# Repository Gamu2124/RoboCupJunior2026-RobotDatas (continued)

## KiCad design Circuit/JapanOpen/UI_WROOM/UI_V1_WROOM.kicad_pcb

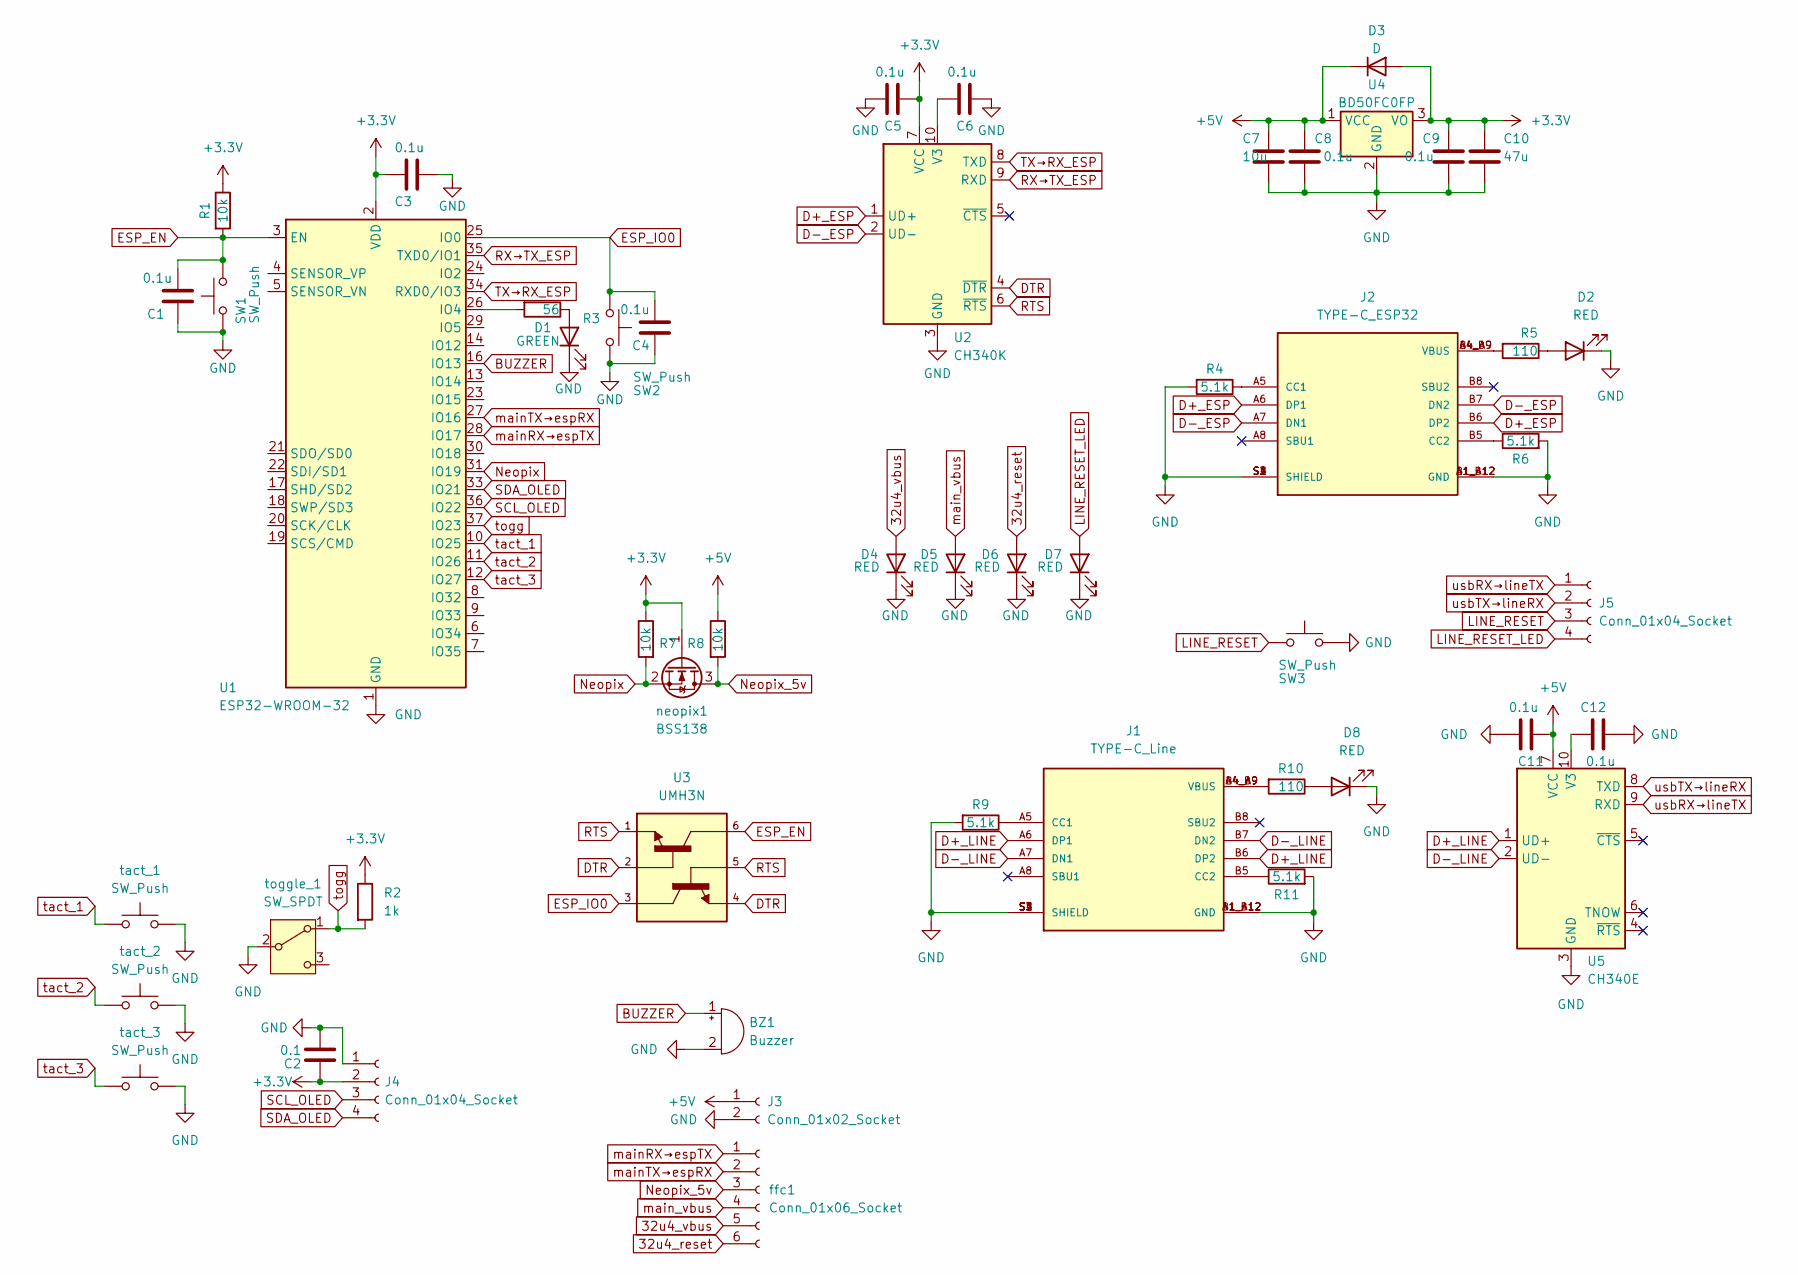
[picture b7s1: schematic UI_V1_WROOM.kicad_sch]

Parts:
BZ1: Buzzer; XDCR_KXG0909P
C1, C3, C4, C5, C6, C8, C9, C11, C12: 0.1u; C_0603_1608Metric_Pad1.08x0.95mm_HandSolder; LCSC C1581
C2: 0.1; C_0603_1608Metric_Pad1.08x0.95mm_HandSolder; LCSC C1581
C7: 10u; C_Disc_D5.1mm_W3.2mm_P5.00mm; LCSC C1713
C10: 47u; CP_Radial_D5.0mm_P2.00mm; LCSC C3337
D1: GREEN; LED_0603_1608Metric_Pad1.05x0.95mm_HandSolder
D2, D4, D5, D6, D7, D8: RED; LED_0603_1608Metric_Pad1.05x0.95mm_HandSolder
D3: D; D_SOD-123F
J1: TYPE-C_Line; NELTRON_5077CR-16SMC2-BK-TR; PARTREV B
J2: TYPE-C_ESP32; NELTRON_5077CR-16SMC2-BK-TR; PARTREV B
J3: Conn_01x02_Socket; JST_XH_B2B-XH-A_1x02_P2.50mm_Vertical
J4: Conn_01x04_Socket; PinSocket_1x04_P2.54mm_Vertical
J5: Conn_01x04_Socket; JST_XH_S4B-XH-A_1x04_P2.50mm_Horizontal
R1: 10k; R_1206_3216Metric; LCSC C26033
R2: 1k; R_Axial_DIN0207_L6.3mm_D2.5mm_P10.16mm_Horizontal
R3: 56; R_1206_3216Metric; LCSC C17909
R4, R6, R9, R11: 5.1k; R_0603_1608Metric_Pad0.98x0.95mm_HandSolder; LCSC C26033
R5, R10: 110; R_1206_3216Metric; LCSC C17909
R7, R8: 10k; R_1206_3216Metric; LCSC C1489
SW1, SW2, SW3: SW_Push; Switch_SKRPABE010
U1: ESP32-WROOM-32
U2: CH340K; SSOP-10-1EP_3.9x4.9mm_P1mm_EP2.1x3.3mm
U3: UMH3N; UMT6
U4: BD50FC0FP; TO-252-2
U5: CH340E; MSOP-10_3x3mm_P0.5mm
ffc1: Conn_01x06_Socket; TE_84952-6_1x06-1MP_P1.0mm_Horizontal
neopix1: BSS138; SOT-23; LCSC C192057
tact_1, tact_2, tact_3: SW_Push; SW_PUSH-12mm
toggle_1: SW_SPDT; PinSocket_1x03_P2.54mm_Vertical

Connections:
32u4_reset: D6.2 (A), ffc1.6
32u4_vbus: D4.2 (A), ffc1.5
+3.3V: C2.1, C3.2, C5.1, C9.1, C10.1, D3.2 (A), J4.2, R1.1, R2.1, R7.1, U1.2 (VDD), U2.7 (VCC), U4.3 (VO), neopix1.1 (G)
+5V: C7.1, C8.1, C11.1, D3.1 (K), J3.1, R8.1, U4.1 (VCC), U5.7 (VCC)
BUZZER: BZ1.1 (+), BZ1.P, U1.16 (IO13)
D+_ESP: J2.A6 (DP1), J2.B6 (DP2), U2.1 (UD+)
D+_LINE: J1.A6 (DP1), J1.B6 (DP2), U5.1 (UD+)
D-_ESP: J2.A7 (DN1), J2.B7 (DN2), U2.2 (UD-)
D-_LINE: J1.A7 (DN1), J1.B7 (DN2), U5.2 (UD-)
DTR: U2.4 (~DTR), U3.2, U3.4
ESP_EN: C1.1, R1.2, SW1.1, U1.3 (EN), U3.6
ESP_IO0: C4.1, SW2.1, U1.25 (IO0), U3.3
GND: BZ1.2 (-), BZ1.N, C1.2, C2.2, C3.1, C4.2, C5.2, C6.1, C7.2, C8.2, C9.2, C10.2, C11.2, C12.2, D1.1 (K), D2.1 (K), D4.1 (K), D5.1 (K), D6.1 (K), D7.1 (K), D8.1 (K), J1.A1_B12 (GND), J1.B1_A12 (GND), J1.S1 (SHIELD), J1.S2 (SHIELD), J1.S3 (SHIELD), J1.S4 (SHIELD), J2.A1_B12 (GND), J2.B1_A12 (GND), J2.S1 (SHIELD), J2.S2 (SHIELD), J2.S3 (SHIELD), J2.S4 (SHIELD), J3.2, J4.1, R4.2, R6.2, R9.2, R11.2, SW1.2, SW2.2, SW3.2, U1.1 (GND), U1.15 (GND), U1.38 (GND), U1.39 (GND), U2.3 (GND), U2.11 (GND), U4.2 (GND), U5.3 (GND), tact_1.2, tact_2.2, tact_3.2, toggle_1.2 (B)
LINE_RESET: J5.3, SW3.1
LINE_RESET_LED: D7.2 (A), J5.4
Neopix: R7.2, U1.31 (IO19), neopix1.2 (S)
Neopix_5v: R8.2, ffc1.3, neopix1.3 (D)
unnamed: D1.2 (A), R3.1
unnamed: D2.2 (A), R5.1
unnamed: D8.2 (A), R10.1
unnamed: J1.A5 (CC1), R9.1
unnamed: J1.B5 (CC2), R11.1
unnamed: J1.A4_B9 (VBUS), J1.B4_A9 (VBUS), R10.2
unnamed: J2.A5 (CC1), R4.1
unnamed: J2.B5 (CC2), R6.1
unnamed: J2.A4_B9 (VBUS), J2.B4_A9 (VBUS), R5.2
unnamed: R3.2, U1.26 (IO4)
unnamed: C6.2, U2.10 (V3)
unnamed: C12.1, U5.10 (V3)
RTS: U2.6 (~RTS), U3.1, U3.5
RX→TX_ESP: U1.35 (TXD0/IO1), U2.9 (RXD)
SCL_OLED: J4.3, U1.36 (IO22)
SDA_OLED: J4.4, U1.33 (IO21)
TX→RX_ESP: U1.34 (RXD0/IO3), U2.8 (TXD)
mainRX→espTX: U1.28 (IO17), ffc1.1
mainTX→espRX: U1.27 (IO16), ffc1.2
main_vbus: D5.2 (A), ffc1.4
tact_1: U1.10 (IO25), tact_1.1
tact_2: U1.11 (IO26), tact_2.1
tact_3: U1.12 (IO27), tact_3.1
togg: R2.2, U1.37 (IO23), toggle_1.1 (A)
usbRX→lineTX: J5.1, U5.9 (RXD)
usbTX→lineRX: J5.2, U5.8 (TXD)

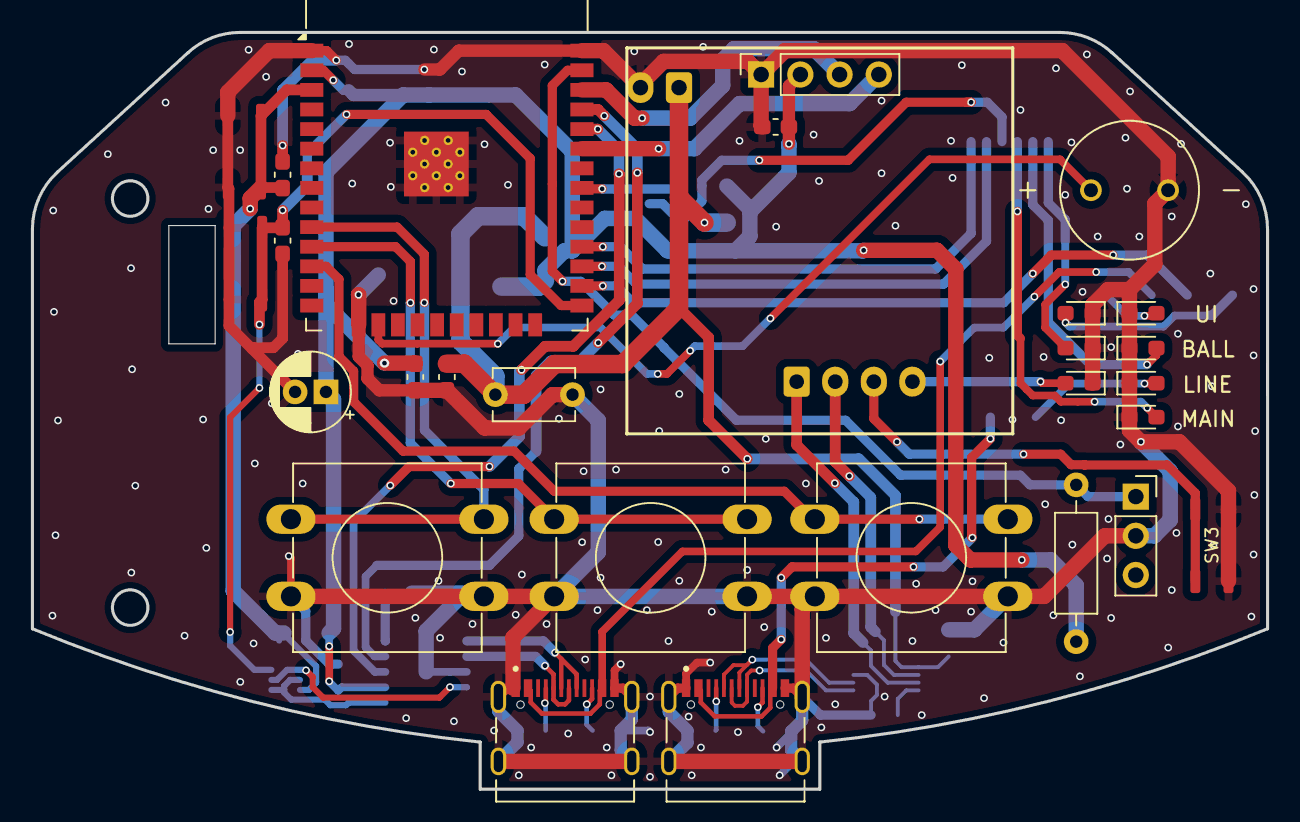
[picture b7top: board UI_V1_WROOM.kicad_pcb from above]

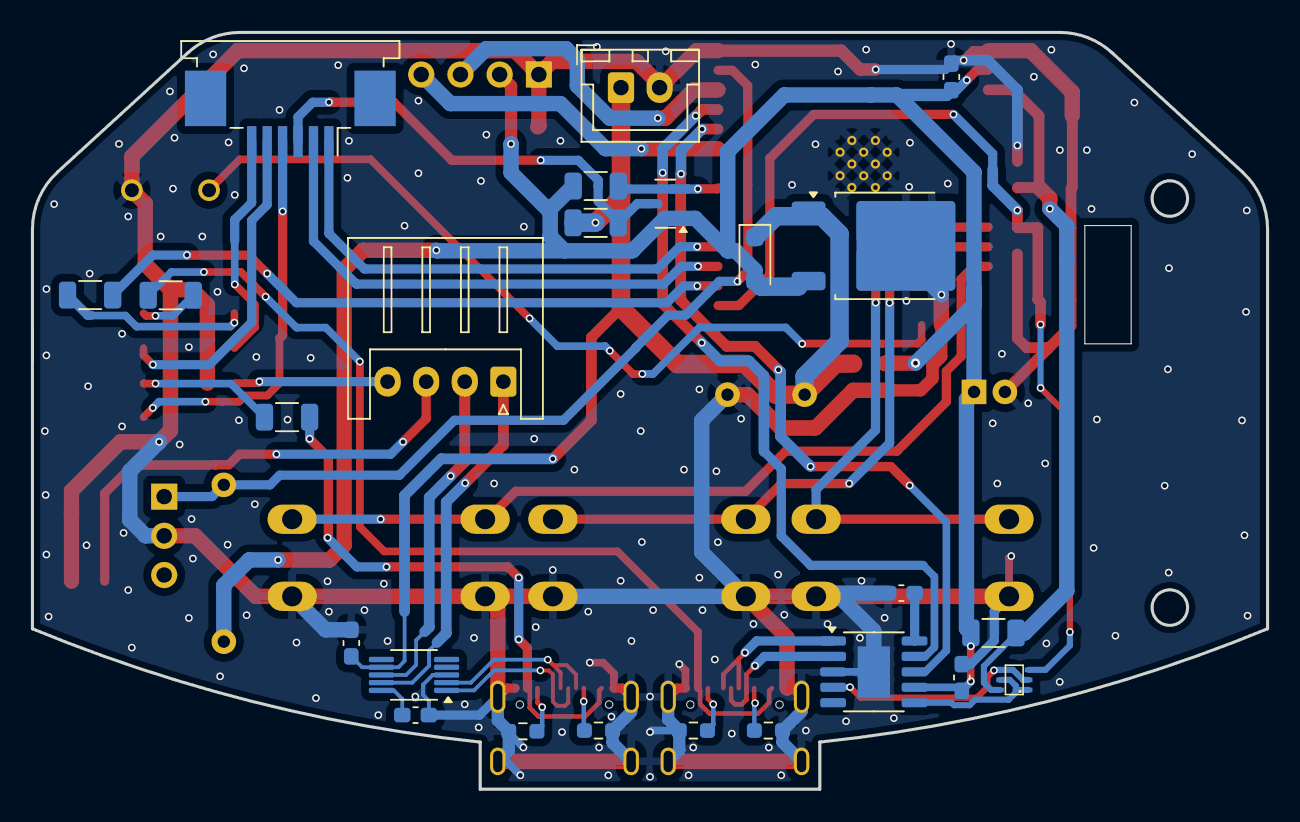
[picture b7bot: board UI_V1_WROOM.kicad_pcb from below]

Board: 2 copper layers, 80.0 x 49.0 mm, 51 parts (24 on the bottom side), 43 nets.

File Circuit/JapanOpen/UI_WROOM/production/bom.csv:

Designator,Footprint,Quantity,Value,LCSC Part #
BZ1,XDCR_KXG0909P,1,Buzzer,
"C1, C11, C12, C3, C4, C5, C6, C8, C9",0603,9,0.1u,C1581
C10,CP_Radial_D5.0mm_P2.00mm,1,47u,C3337
C2,0603,1,0.1,C1581
C7,C_Disc_D5.1mm_W3.2mm_P5.00mm,1,10u, C1713
D1,0603,1,GREEN,
"D2, D4, D5, D6, D7, D8",0603,6,RED,
D3,D_SOD-123F,1,D,
FFC1,TE_84952-6_1x06-1MP_P1.0mm_Horizontal,1,Conn_01x06_Socket,
J1,NELTRON_5077CR-16SMC2-BK-TR,1,TYPE-C_Line,
J2,NELTRON_5077CR-16SMC2-BK-TR,1,TYPE-C_ESP32,
J3,JST_XH_B2B-XH-A_1x02_P2.50mm_Vertical,1,Conn_01x02_Socket,
J4,PinSocket_1x04_P2.54mm_Vertical,1,Conn_01x04_Socket,
J5,JST_XH_S4B-XH-A_1x04_P2.50mm_Horizontal,1,Conn_01x04_Socket,
NEOPIX1,SOT-23,1,BSS138, C192057
R1,1206,1,10k,C26033
"R10, R5",1206,2,110,C17909
"R11, R4, R6, R9",0603,4,5.1k,C26033
R2,R_Axial_DIN0207_L6.3mm_D2.5mm_P10.16mm_Horizontal,1,1k,
R3,1206,1,56,C17909
"R7, R8",1206,2,10k, C1489
"SW1, SW2, SW3",Switch_SKRPABE010,3,SW_Push,
"TACT_1, TACT_2, TACT_3",SW_PUSH-12mm,3,SW_Push,
TOGGLE_1,PinSocket_1x03_P2.54mm_Vertical,1,SW_SPDT,
U1,ESP32-WROOM-32,1,ESP32-WROOM-32,
U2,SSOP-10-1EP_3.9x4.9mm_P1mm_EP2.1x3.3mm,1,CH340K,
U3,UMT6,1,UMH3N,
U4,TO-252-2,1,BD50FC0FP,
U5,MSOP-10_3x3mm_P0.5mm,1,CH340E,

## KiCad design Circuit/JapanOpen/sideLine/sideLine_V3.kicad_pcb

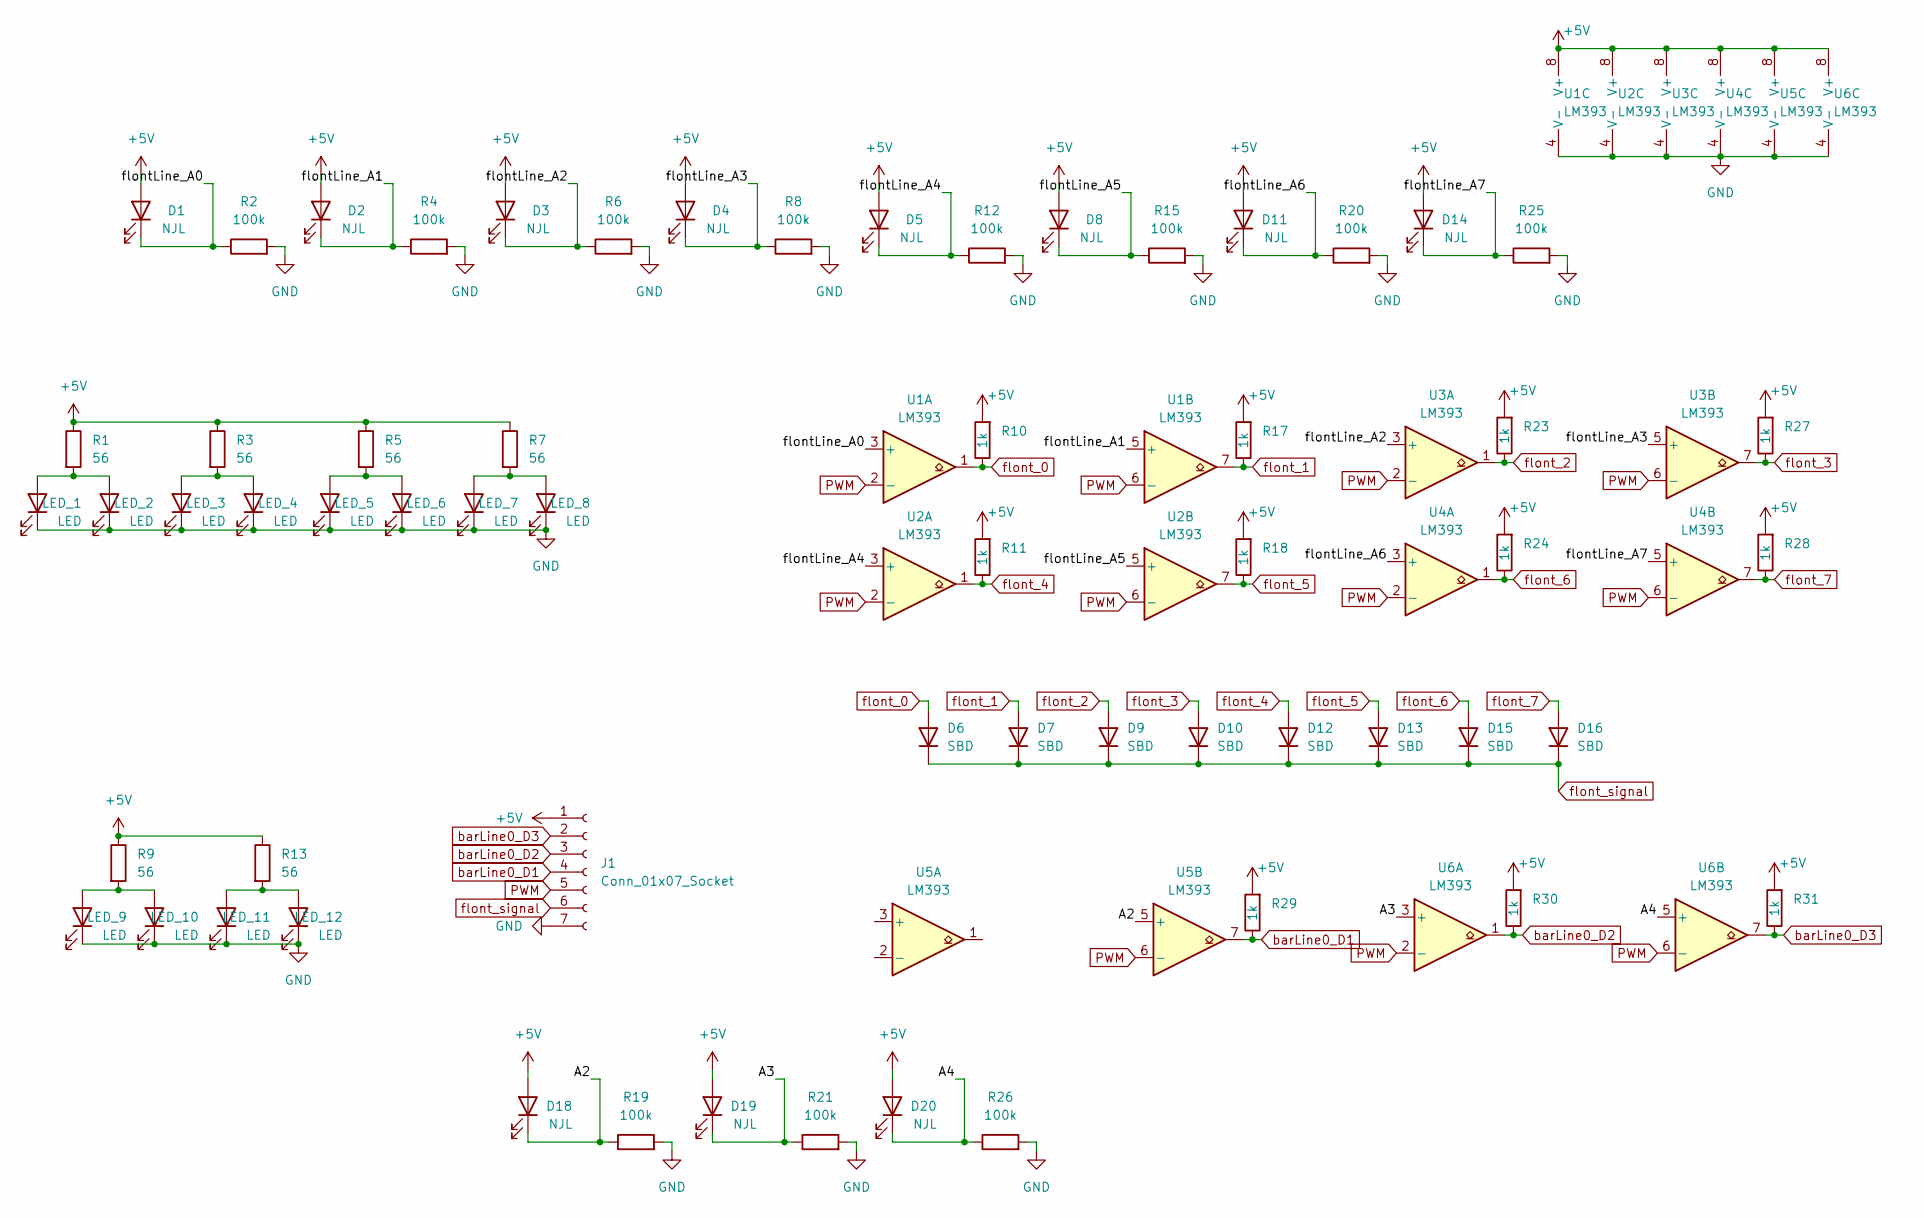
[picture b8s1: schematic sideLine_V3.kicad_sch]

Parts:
D1, D2, D3, D4, D5, D8, D11, D14, D18, D19, D20: NJL; LED_0603_1608Metric
D6, D7, D9, D10, D12, D13, D15, D16: SBD; D_SOD-323
J1: Conn_01x07_Socket; PinSocket_1x07_P2.54mm_Vertical
LED_1, LED_2, LED_3, LED_4, LED_5, LED_6, LED_7, LED_8, LED_9, LED_10, LED_11, LED_12: LED; LED_0603_1608Metric_Pad1.05x0.95mm_HandSolder
R1, R3, R5, R7, R9, R13: 56; R_1206_3216Metric; LCSC C17995
R2, R4, R6, R8, R12, R15, R19, R20, R21, R25, R26: 100k; R_0603_1608Metric; LCSC C23098
R10, R11, R17, R18, R23, R24, R27, R28, R29, R30, R31: 1k; R_0603_1608Metric; LCSC C23098
U1, U2, U3, U4, U5, U6: LM393; SOIC-8_3.9x4.9mm_P1.27mm

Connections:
+5V: D1.2 (A), D2.2 (A), D3.2 (A), D4.2 (A), D5.2 (A), D8.2 (A), D11.2 (A), D14.2 (A), D18.2 (A), D19.2 (A), D20.2 (A), J1.1, R1.1, R3.1, R5.1, R7.1, R9.1, R10.2, R11.2, R13.1, R17.2, R18.2, R23.2, R24.2, R27.2, R28.2, R29.2, R30.2, R31.2, U1.8 (V+), U2.8 (V+), U3.8 (V+), U4.8 (V+), U5.8 (V+), U6.8 (V+)
/A2: D18.1 (K), R19.1, U5.5 (+)
/A3: D19.1 (K), R21.1, U6.3 (+)
/A4: D20.1 (K), R26.1, U6.5 (+)
/flontLine_A0: D1.1 (K), R2.1, U1.3 (+)
/flontLine_A1: D2.1 (K), R4.1, U1.5 (+)
/flontLine_A2: D3.1 (K), R6.1, U3.3 (+)
/flontLine_A3: D4.1 (K), R8.1, U3.5 (+)
/flontLine_A4: D5.1 (K), R12.1, U2.3 (+)
/flontLine_A5: D8.1 (K), R15.1, U2.5 (+)
/flontLine_A6: D11.1 (K), R20.1, U4.3 (+)
/flontLine_A7: D14.1 (K), R25.1, U4.5 (+)
GND: J1.7, LED_1.1 (K), LED_2.1 (K), LED_3.1 (K), LED_4.1 (K), LED_5.1 (K), LED_6.1 (K), LED_7.1 (K), LED_8.1 (K), LED_9.1 (K), LED_10.1 (K), LED_11.1 (K), LED_12.1 (K), R2.2, R4.2, R6.2, R8.2, R12.2, R15.2, R19.2, R20.2, R21.2, R25.2, R26.2, U1.4 (V-), U2.4 (V-), U3.4 (V-), U4.4 (V-), U5.4 (V-), U6.4 (V-)
unnamed: LED_1.2 (A), LED_2.2 (A), R1.2
unnamed: LED_3.2 (A), LED_4.2 (A), R3.2
unnamed: LED_5.2 (A), LED_6.2 (A), R5.2
unnamed: LED_7.2 (A), LED_8.2 (A), R7.2
unnamed: LED_9.2 (A), LED_10.2 (A), R9.2
unnamed: LED_11.2 (A), LED_12.2 (A), R13.2
PWM: J1.5, U1.2 (-), U1.6 (-), U2.2 (-), U2.6 (-), U3.2 (-), U3.6 (-), U4.2 (-), U4.6 (-), U5.6 (-), U6.2 (-), U6.6 (-)
barLine0_D1: J1.4, R29.1, U5.7
barLine0_D2: J1.3, R30.1, U6.1
barLine0_D3: J1.2, R31.1, U6.7
flont_0: D6.2 (A), R10.1, U1.1
flont_1: D7.2 (A), R17.1, U1.7
flont_2: D9.2 (A), R23.1, U3.1
flont_3: D10.2 (A), R27.1, U3.7
flont_4: D12.2 (A), R11.1, U2.1
flont_5: D13.2 (A), R18.1, U2.7
flont_6: D15.2 (A), R24.1, U4.1
flont_7: D16.2 (A), R28.1, U4.7
flont_signal: D6.1 (K), D7.1 (K), D9.1 (K), D10.1 (K), D12.1 (K), D13.1 (K), D15.1 (K), D16.1 (K), J1.6

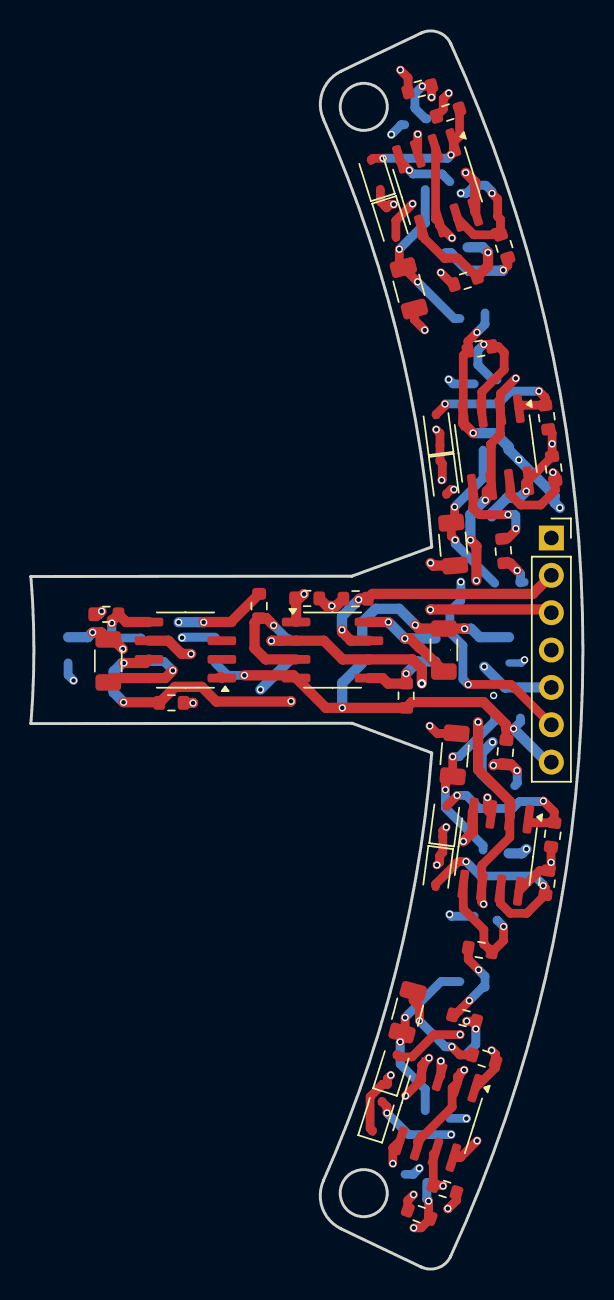
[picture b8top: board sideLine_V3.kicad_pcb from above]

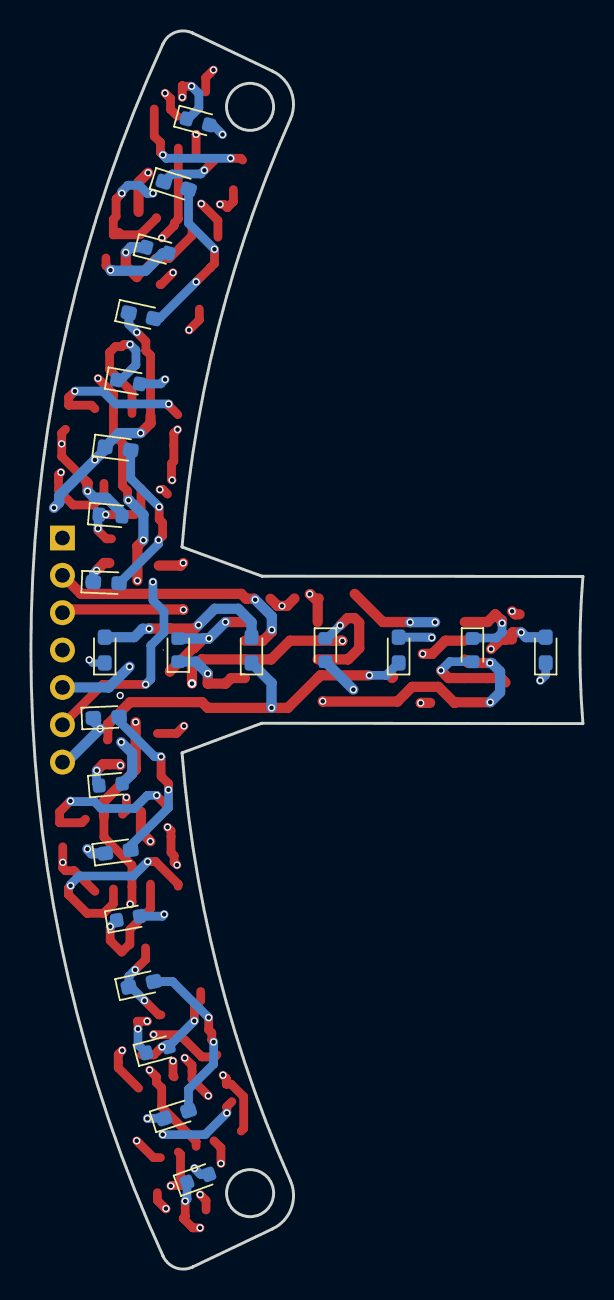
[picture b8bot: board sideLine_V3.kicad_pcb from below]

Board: 4 copper layers, 37.5 x 84.2 mm, 66 parts (23 on the bottom side), 32 nets.

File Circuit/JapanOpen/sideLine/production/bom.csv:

Designator,Footprint,Quantity,Value,LCSC Part #
"D1, D11, D14, D18, D19, D2, D20, D3, D4, D5, D8",0603,11,NJL,
"D10, D12, D13, D15, D16, D6, D7, D9",D_SOD-323,8,SBD,
J1,PinSocket_1x07_P2.54mm_Vertical,1,Conn_01x07_Socket,
"LED_1, LED_10, LED_11, LED_12, LED_2, LED_3, LED_4, LED_5, LED_6, LED_7, LED_8, LED_9",0603,12,LED,
"R1, R13, R3, R5, R7, R9",1206,6,56,C17995
"R10, R11, R17, R18, R23, R24, R27, R28, R29, R30, R31",0603,11,1k,C23098
"R12, R15, R19, R2, R20, R21, R25, R26, R4, R6, R8",0603,11,100k,C23098
"U1, U2, U3, U4, U5, U6",SOIC-8_3.9x4.9mm_P1.27mm,6,LM393,

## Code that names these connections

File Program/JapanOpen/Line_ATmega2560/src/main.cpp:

#include <Arduino.h>

// ピン情報の定義
volatile uint8_t* pins[] = {
  &PIND, &PIND, &PINL, &PINL, &PINL, &PINL, &PINH, &PINH,
  &PINH, &PINH, &PINH, &PINH, &PINJ, &PINJ, &PINJ, &PINJ,
  &PINJ, &PINC, &PINC, &PINC, &PINC, &PINC, &PINC, &PINC
};

uint8_t bits[] = {
  7, 6, 7, 6, 5, 4, 6, 5,
  4, 3, 2, 1, 7, 6, 5, 4,
  3, 7, 6, 5, 4, 3, 2, 1
};

// デバッグ表示用関数
void debugPrint(uint8_t b0, uint8_t b1, uint8_t b2, uint8_t side_grid);

void setup() {
  Serial.begin(9600);  // PCデバッグ用
  Serial1.begin(115200); // Teensy通信用
  // 入力ピン初期化
  DDRA &= ~(_BV(PA2) | _BV(PA6) | _BV(PA5));
  DDRD &= ~(_BV(PD7) | _BV(PD6));
  DDRL &= ~(_BV(PL7) | _BV(PL6) | _BV(PL5) | _BV(PL4));
  DDRH &= ~(_BV(PH6) | _BV(PH5) | _BV(PH4) | _BV(PH3) | _BV(PH2) | _BV(PH1));
  DDRJ &= ~(_BV(PJ7) | _BV(PJ6) | _BV(PJ5) | _BV(PJ4) | _BV(PJ3) | _BV(PJ0));
  DDRC &= ~(_BV(PC7) | _BV(PC6) | _BV(PC5) | _BV(PC4) | _BV(PC3) | _BV(PC2) | _BV(PC1));
  DDRF &= ~(_BV(PF0) | _BV(PF1) | _BV(PF3) | _BV(PF6));
  DDRK &= ~(_BV(PK0) | _BV(PK1) | _BV(PK4) | _BV(PK5) | _BV(PK6));
  pinMode(5, OUTPUT);
  TCCR3B = (TCCR3B & 0xF8) | 0x01; 
  analogWrite(5, 85); //26朝150 //80
}

void loop() {
  // unsigned long startTime = micros(); // 開始（マイクロ秒） 
  // 1. ラインセンサーパッキング
  uint8_t b0 = 0, b1 = 0, b2 = 0;
  for (int i = 0; i < 8; i++)  if ((*pins[i] >> bits[i]) & 0x01) b0 |= (1 << i);
  for (int i = 8; i < 16; i++) if ((*pins[i] >> bits[i]) & 0x01) b1 |= (1 << (i - 8));
  for (int i = 16; i < 24; i++)if ((*pins[i] >> bits[i]) & 0x01) b2 |= (1 << (i - 16));

  // 2. サイド & Gridパッキング
  uint8_t side_grid = 0;
  if ((PINA >> 2) & 0x01) side_grid |= (1 << 7); // F
  if ((PINF >> 6) & 0x01) side_grid |= (1 << 6); // L
  if ((PINA >> 6) & 0x01) side_grid |= (1 << 5); // R
  if ((PINA >> 5) & 0x01) side_grid |= (1 << 4); // B

  if (((PINF >> 0) | (PINF >> 1) | (PINF >> 3)) & 0x01) side_grid |= (1 << 3); // GL
  // if (((PINK >> 0) | (PINK >> 1) | (PINJ >> 0)) & 0x01) side_grid |= (1 << 2); // GR
  if (((PINK >> 4) | (PINK >> 5) | (PINK >> 6)) & 0x01) side_grid |= (1 << 1); // GB

  // 3. パケット送信 (6バイト)
  Serial1.write(255);       // Header
  Serial1.write(b0);
  Serial1.write(b1);
  Serial1.write(b2);
  Serial1.write(side_grid);
  Serial1.write(128);       // Footer

  // debugPrint(b0, b1, b2, side_grid);
}

// デバッグ用関数：シリアルモニタで人間が読みやすい形式で表示
void debugPrint(uint8_t b0, uint8_t b1, uint8_t b2, uint8_t side_grid) {
  static uint32_t lastPrint = 0;
  if (millis() - lastPrint < 50) return; // 表示が速すぎて読めないのを防ぐ(20Hz)
  lastPrint = millis();

  Serial.print("L:");
  // 24bit分をバイナリ表示
  for(int i=0; i<8; i++) Serial.print((b0 >> i) & 1);
  for(int i=0; i<8; i++) Serial.print((b1 >> i) & 1);
  for(int i=0; i<8; i++) Serial.print((b2 >> i) & 1);

  Serial.print(" | S(FLRB):");
  Serial.print((side_grid >> 7) & 1);
  Serial.print((side_grid >> 6) & 1);
  Serial.print((side_grid >> 5) & 1);
  Serial.print((side_grid >> 4) & 1);

  Serial.print(" | G(LRB):");
  Serial.print((side_grid >> 3) & 1);
  Serial.print((side_grid >> 2) & 1);
  Serial.print((side_grid >> 1) & 1);
  Serial.println();
}

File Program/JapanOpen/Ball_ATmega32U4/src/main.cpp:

#include <Arduino.h>
#include <math.h>

const uint8_t ARR_LENGTH = 5;
int Ball_num[ARR_LENGTH];
int arr_center = 2;
uint8_t first = 0;
uint8_t Ball_digital[16];
uint8_t Ball_count[16];
uint8_t Ball_best_val = 0;
uint8_t Ball_sum = 0;
uint8_t Ball_best_num = 0;

byte sendBuf_byte[8];

void get_Ball();
void print();

float pretime = 0;

void setup(){
    /* ===== 入力ピン設定 ===== */
    DDRC &= ~((1 << PC7) | (1 << PC6));               // PC7, PC6
    DDRB &= ~((1 << PB6) | (1 << PB5) | (1 << PB4) |  // PB6..PB0
              (1 << PB3) | (1 << PB2) | (1 << PB1) | (1 << PB0));
    DDRD &= ~((1 << PD7) | (1 << PD6) | (1 << PD4)); // PD7, PD6, PD4
    DDRF &= ~((1 << PF0) | (1 << PF1) | (1 << PF4) | (1 << PF5)); // PF系

    Serial1.begin(115200);
    Serial.begin(9600);

    while (!Serial1) {}
    delay(1500);
}

void loop(){
    get_Ball();

    sendBuf_byte[0] = 0xFF;

    if(Ball_sum == 0){
        for(int i = 1; i <= 6; i++){
            sendBuf_byte[i] = 0x80;
        }
    } else {
        sendBuf_byte[1] = Ball_best_num;
        sendBuf_byte[2] = Ball_count[Ball_num[0]];
        sendBuf_byte[3] = Ball_count[Ball_num[1]];
        sendBuf_byte[4] = Ball_count[Ball_num[2]];
        sendBuf_byte[5] = Ball_count[Ball_num[3]];
        sendBuf_byte[6] = Ball_count[Ball_num[4]];
    }

    sendBuf_byte[7] = 0;
    Serial1.write(sendBuf_byte, 8);
}

void get_Ball()
{
    memset(Ball_count, 0, sizeof(Ball_count));
    memset(Ball_num, 0, sizeof(Ball_num));

    Ball_best_val = 0;
    Ball_sum = 0;
    Ball_best_num = 0;

    for(int j = 0; j < 80; j++){
        Ball_digital[0]  = PINC & _BV(7); // PC7
        Ball_digital[1]  = PINC & _BV(6); // PC6
        Ball_digital[2]  = PINB & _BV(6); // PB6
        Ball_digital[3]  = PINB & _BV(5); // PB5
        Ball_digital[4]  = PINB & _BV(4); // PB4
        Ball_digital[5]  = PIND & _BV(7); // PD7
        Ball_digital[6]  = PIND & _BV(6); // PD6
        Ball_digital[7]  = PIND & _BV(4); // PD4
        Ball_digital[8]  = PINB & _BV(3); // PB3
        Ball_digital[9]  = PINB & _BV(2); // PB2
        Ball_digital[10] = PINB & _BV(1); // PB1
        Ball_digital[11] = PINB & _BV(0); // PB0
        Ball_digital[12] = PINF & _BV(0); // PF0
        Ball_digital[13] = PINF & _BV(1); // PF1
        Ball_digital[14] = PINF & _BV(4); // PF4
        Ball_digital[15] = PINF & _BV(5); // PF5

        for(int i = 0; i < 16; i++){
            if(Ball_digital[i] == 0){
                Ball_count[i]++;
                Ball_sum++;
            }
        }
    }

    for(int i = 0; i < 16; i++){
        if(Ball_best_val < Ball_count[i]){
            Ball_best_val = Ball_count[i];
            Ball_best_num = i;
        }
    }

    for(int i = 0; i < ARR_LENGTH; i++){
        Ball_num[i] = Ball_best_num + (i - arr_center);
        if(Ball_num[i] < 0)  Ball_num[i] += 16;
        if(Ball_num[i] > 15) Ball_num[i] -= 16;
    }
}

void print(){
    Serial.print("best : ");
    Serial.println(Ball_best_num);
}
